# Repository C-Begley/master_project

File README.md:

# MEng Individual Project ENG5041PA Hardware and Software Emulation Testbed for CubeSat Design

## Abstract
CubeSats are praised for reducing the cost of access to space and increasing opportunities for universities and small organisations to carry out space related research. In principal, a small team with an innovative solution could rapidly develop and fly hardware in space using already existing building 'block' components. However, they still require technical electronic knowledge for the construction and testing of designs. While technical knowledge will always be required, especially on custom built CubeSats, this project aimed to reduce this barrier of entry, by providing a test bed framework to program and experiment with potential CubeSat designs.

The project has two main aims: the construction of physical devices for use in testing and developing accompanying software to help use these devices. The main physical device is a FlatSat, which aims to be generic and suitable for a range of projects. It uses PC/104 Plus connectors and has access to power and diagnostic connections. Alongside the FlatSat, there is a mainboard and battery board from an open source CubeSat design, which can be used to test other CubeSat subsystems. 

The project software helps schedule tasks to be run using the mainboard and FlatSat system. These tasks then act as emulations of an entire CubeSat subsystem. This allows for a subsystem to be tested, as if an entire CubeSat had already been constructed. The framework for programming and using this software, strives to be simple enough for those inexperienced with programming to be able to be use, while still giving enough complexity that most aspects of a CubeSat can be emulated.

To demonstrate the usability of the system, two demonstration boards have been constructed. These boards provide example emulations of payload and communication boards. They also provide a template that can be modified to construct and emulate other subsystems.  A demonstration task schedule has also been created to show how devices can interact with the software and mainboard from this project.

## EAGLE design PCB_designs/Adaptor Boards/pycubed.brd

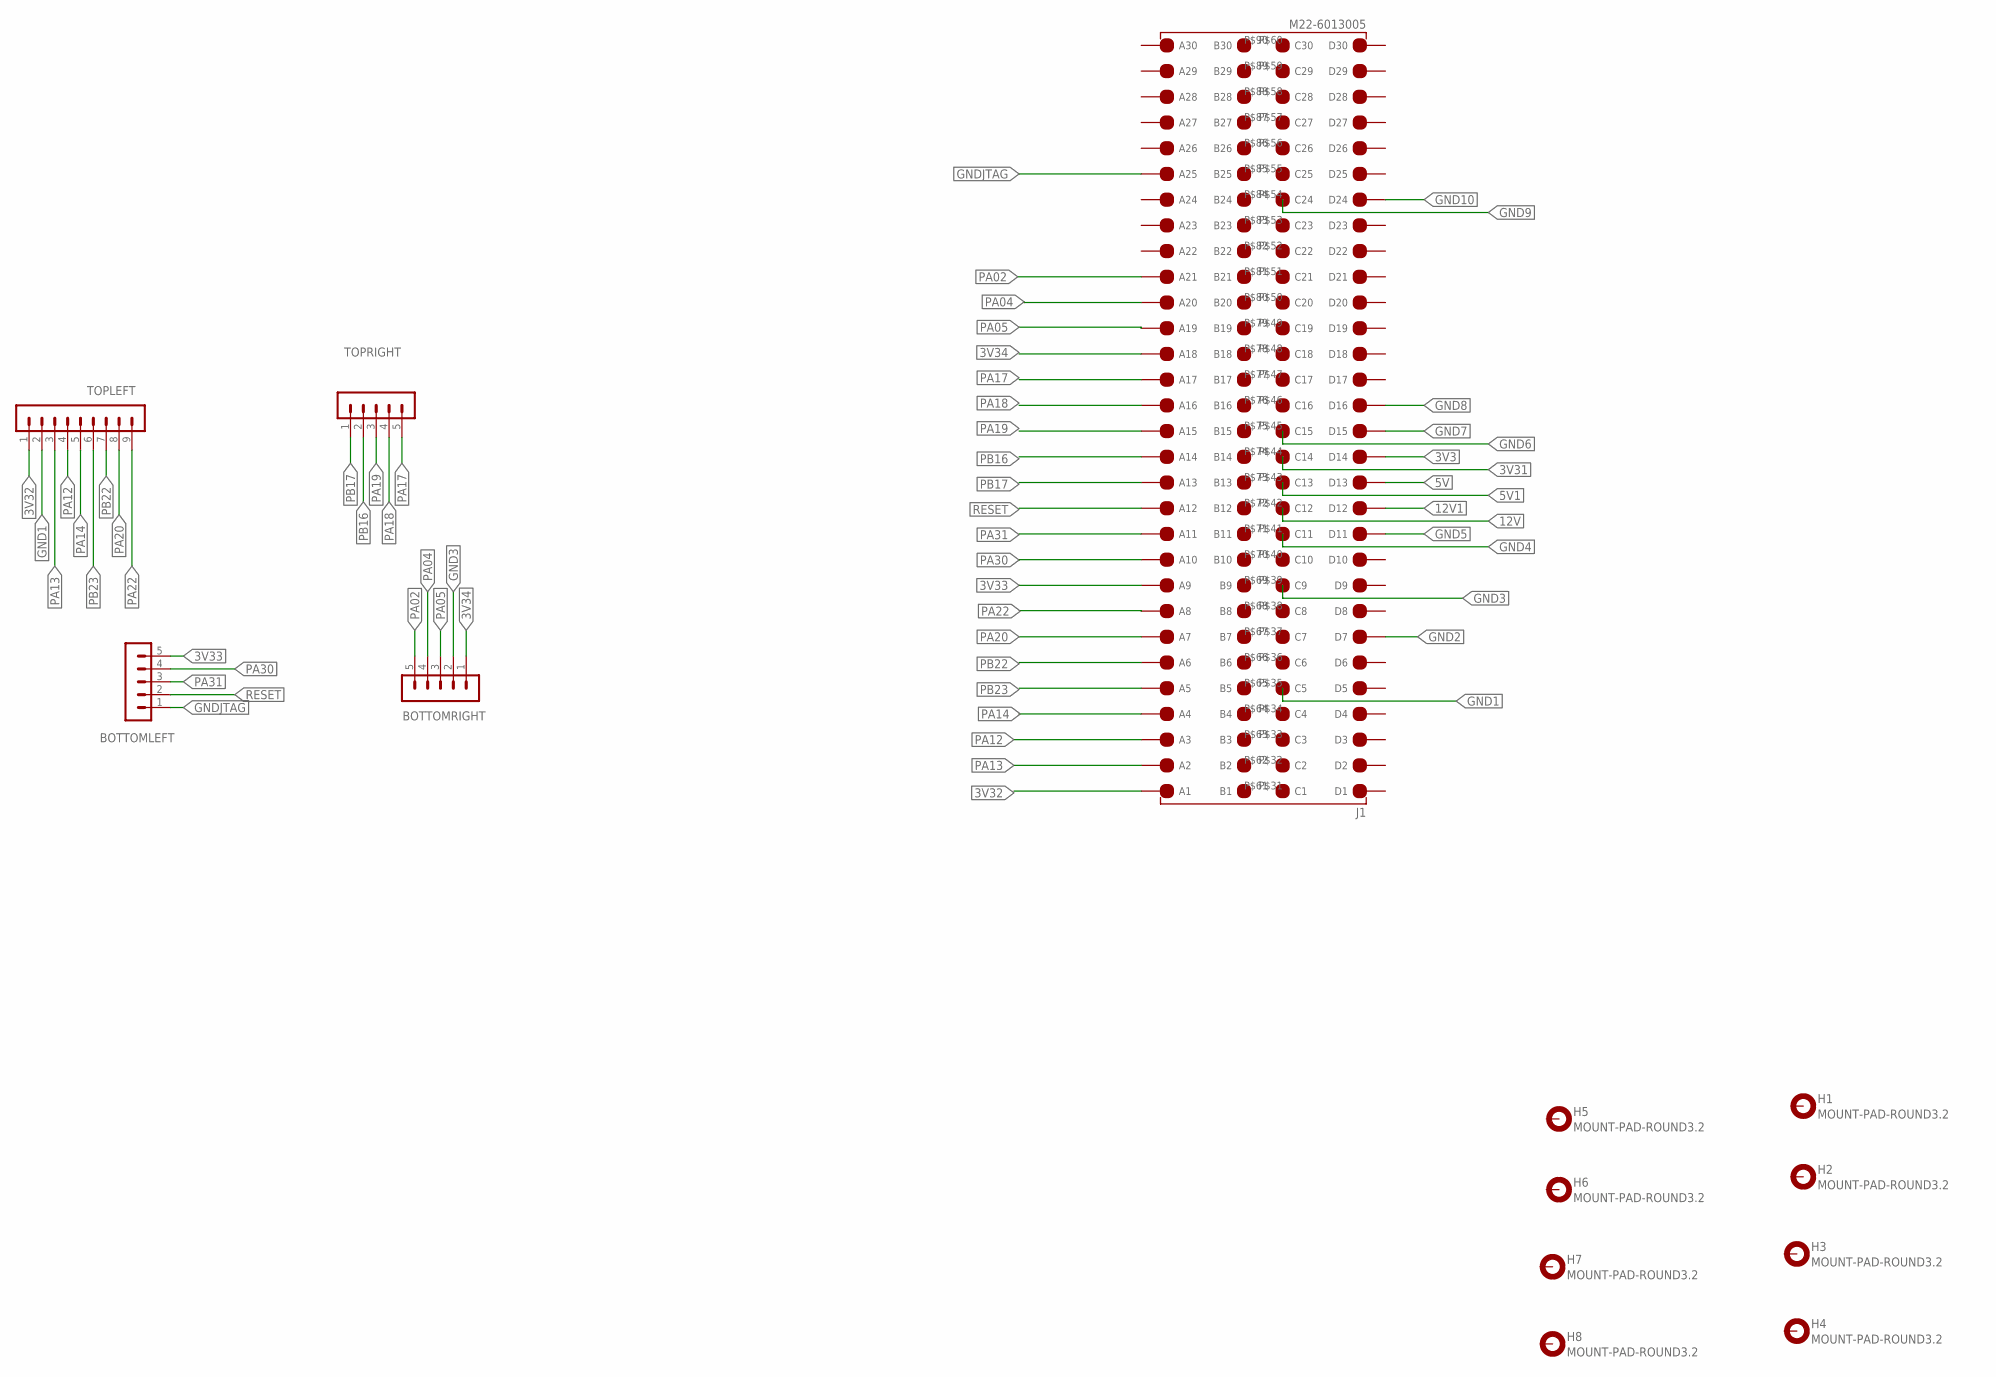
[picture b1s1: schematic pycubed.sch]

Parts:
BOTTOMLEFT: MA05-1
BOTTOMRIGHT: MA05-1
H1, H2, H3, H4, H5, H6, H7, H8: MOUNT-PAD-ROUND3.2; 3,2-PAD
J1: M22-6013005; RHDR120W55P200_4X30_6020X820X9
TOPLEFT: MA09-1
TOPRIGHT: MA05-1

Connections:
3V3: J1.P$14 (D14)
3V31: J1.P$44 (C14)
3V32: J1.P$91 (A1), TOPLEFT.1
3V33: BOTTOMLEFT.5, J1.P$99 (A9)
3V34: BOTTOMRIGHT.1, J1.P$108 (A18)
5V: J1.P$13 (D13)
5V1: J1.P$43 (C13)
12V: J1.P$42 (C12)
12V1: J1.P$12 (D12)
GND1: J1.P$35 (C5), TOPLEFT.2
GND2: J1.P$7 (D7)
GND3: BOTTOMRIGHT.2, J1.P$39 (C9)
GND4: J1.P$41 (C11)
GND5: J1.P$11 (D11)
GND6: J1.P$45 (C15)
GND7: J1.P$15 (D15)
GND8: J1.P$16 (D16)
GND9: J1.P$54 (C24)
GND10: J1.P$24 (D24)
GNDJTAG: BOTTOMLEFT.1, J1.P$115 (A25)
PA02: BOTTOMRIGHT.5, J1.P$111 (A21)
PA04: BOTTOMRIGHT.4, J1.P$110 (A20)
PA05: BOTTOMRIGHT.3, J1.P$109 (A19)
PA12: J1.P$93 (A3), TOPLEFT.4
PA13: J1.P$92 (A2), TOPLEFT.3
PA14: J1.P$94 (A4), TOPLEFT.5
PA17: J1.P$107 (A17), TOPRIGHT.5
PA18: J1.P$106 (A16), TOPRIGHT.4
PA19: J1.P$105 (A15), TOPRIGHT.3
PA20: J1.P$97 (A7), TOPLEFT.8
PA22: J1.P$98 (A8), TOPLEFT.9
PA30: BOTTOMLEFT.4, J1.P$100 (A10)
PA31: BOTTOMLEFT.3, J1.P$101 (A11)
PB16: J1.P$104 (A14), TOPRIGHT.2
PB17: J1.P$103 (A13), TOPRIGHT.1
PB22: J1.P$96 (A6), TOPLEFT.7
PB23: J1.P$95 (A5), TOPLEFT.6
RESET: BOTTOMLEFT.2, J1.P$102 (A12)

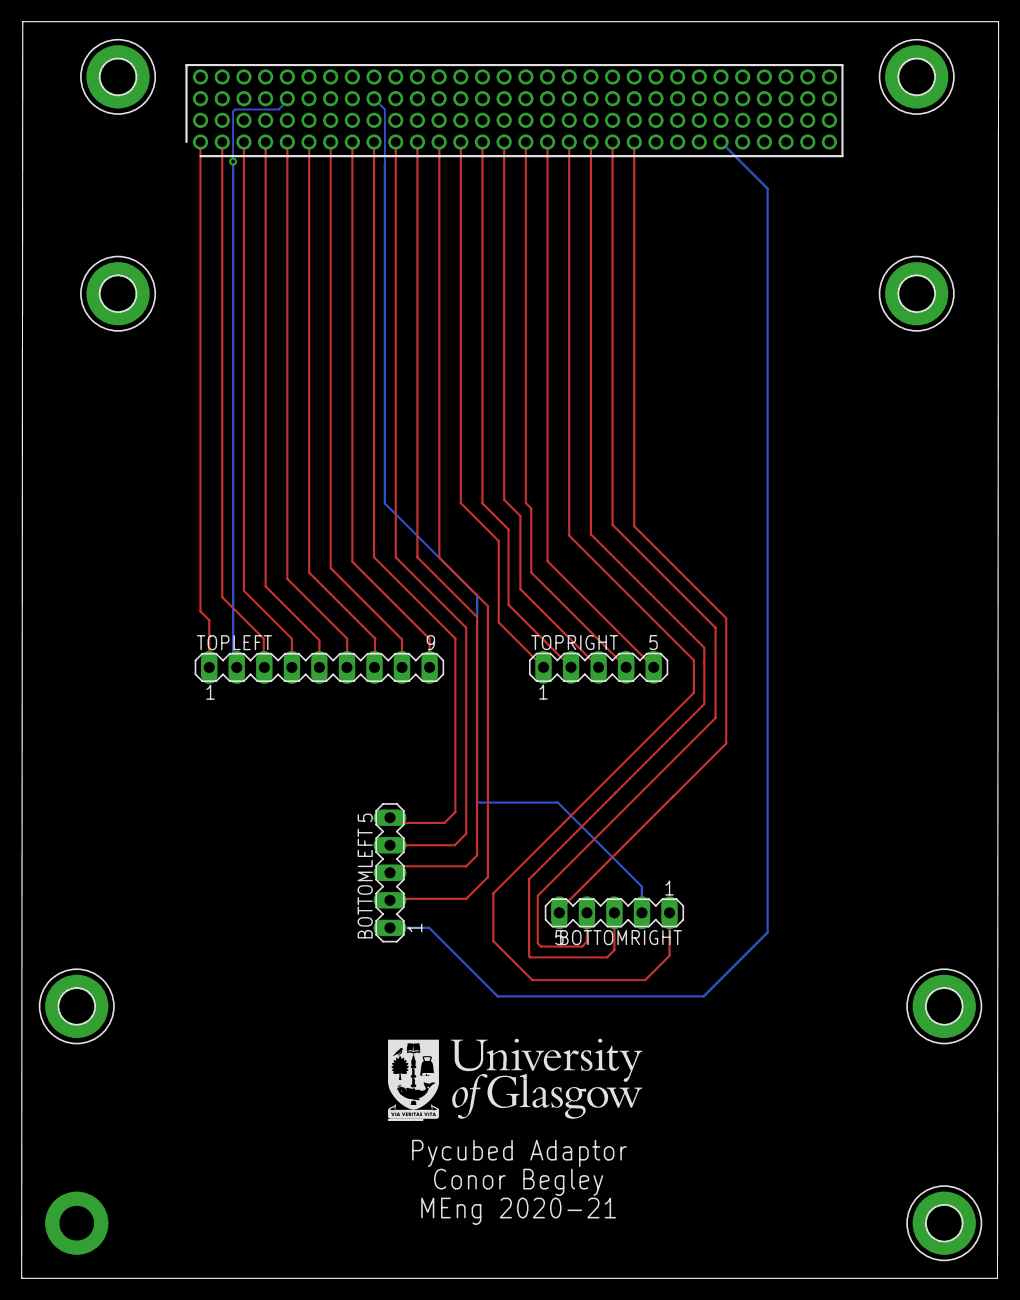
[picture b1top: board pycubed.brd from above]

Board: 2 copper layers, 90.1 x 115.9 mm, 13 parts (1 on the bottom side), 24 nets.

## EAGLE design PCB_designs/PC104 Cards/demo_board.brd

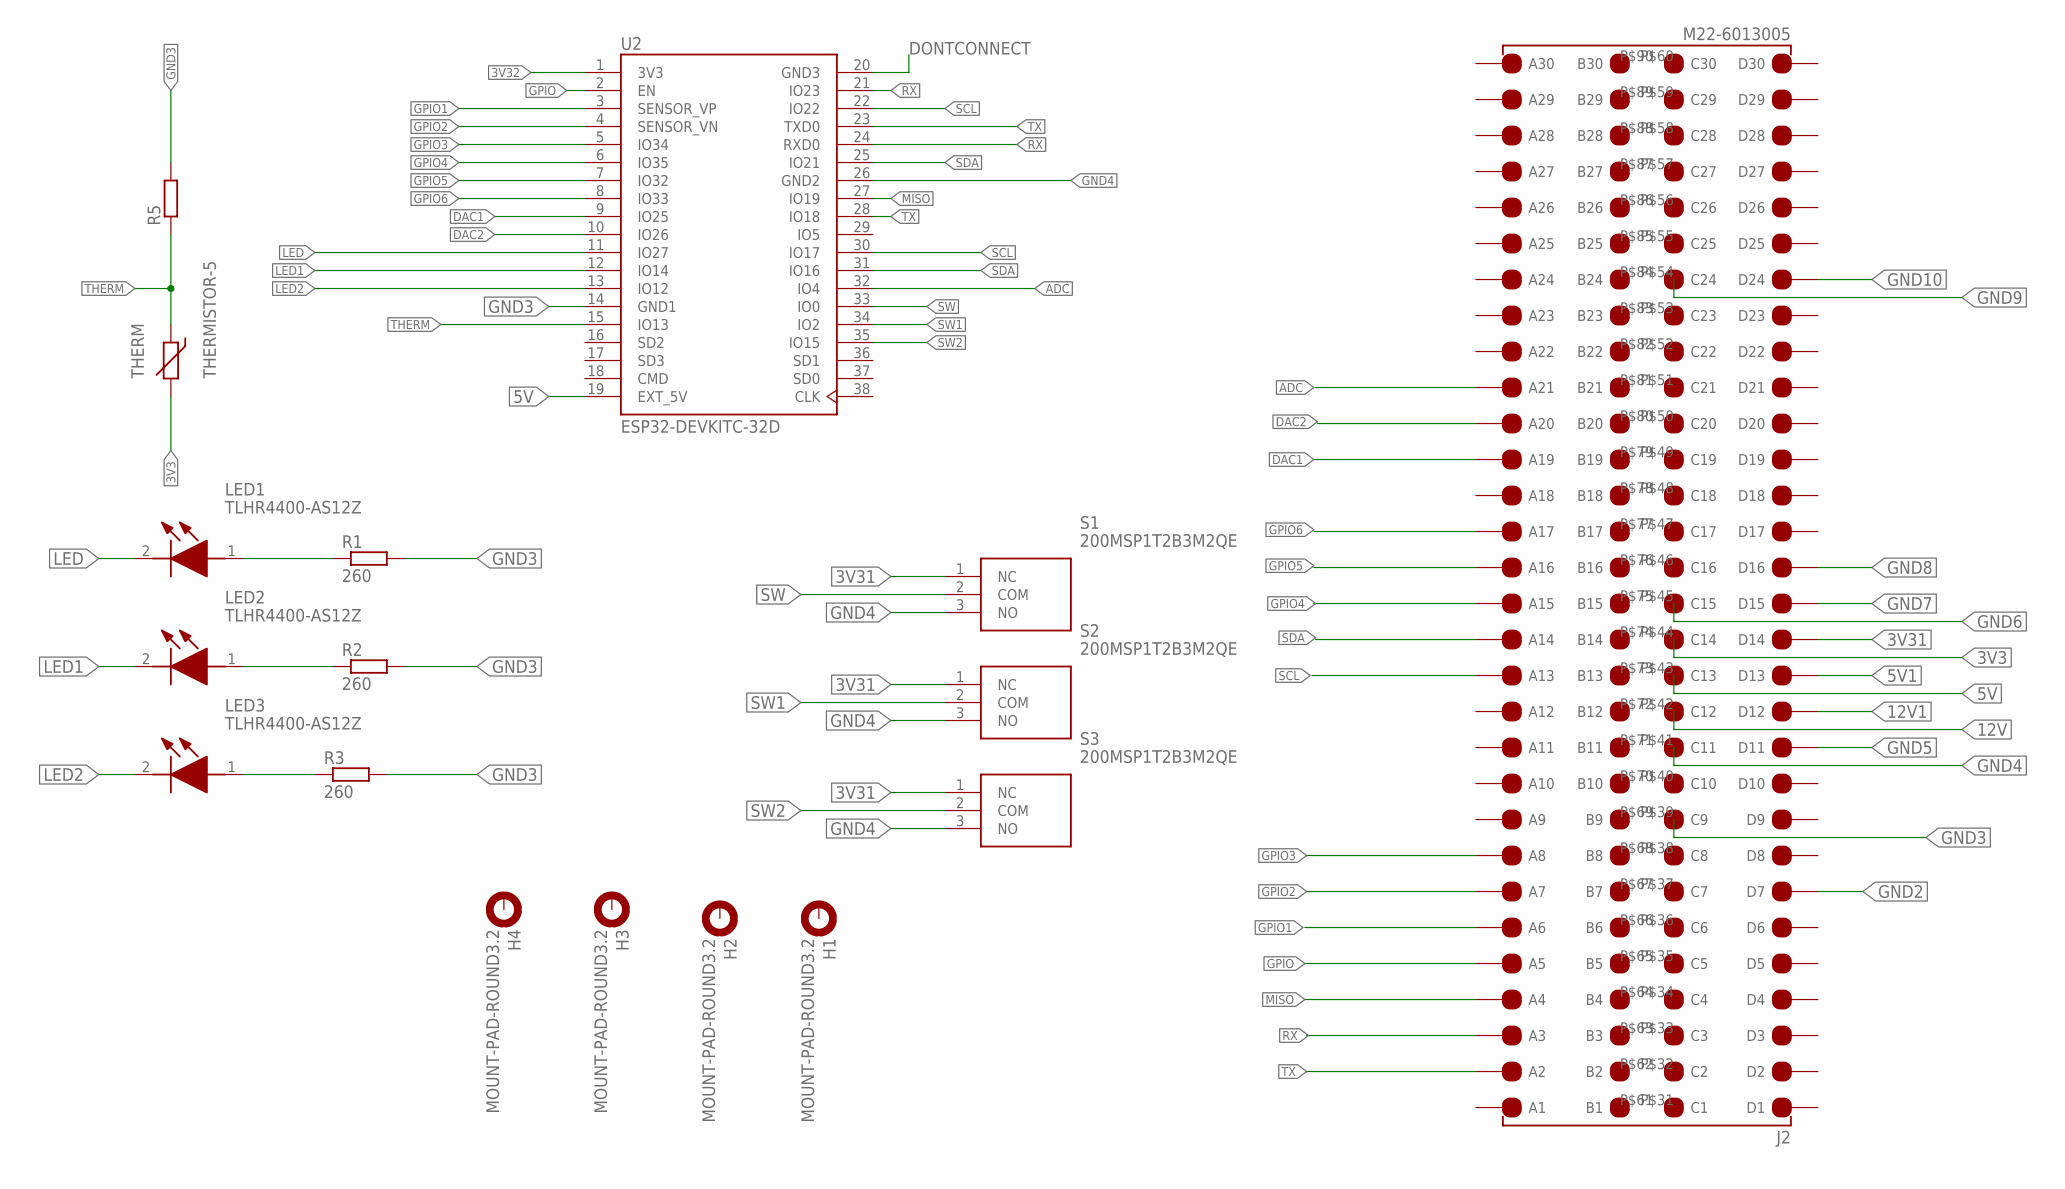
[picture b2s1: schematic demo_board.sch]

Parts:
H1, H2, H3, H4: MOUNT-PAD-ROUND3.2; 3,2-PAD
J2: M22-6013005; RHDR120W55P200_4X30_6020X820X9
LED1, LED2, LED3: TLHR4400-AS12Z; TLHR4400AS12Z
R1, R2, R3: 260; 0204/7
R5: 130; 0204/7
S1, S2, S3: 200MSP1T2B3M2QE
THERM: THERMISTOR-5; R-5
U2: ESP32-DEVKITC-32D; MODULE_ESP32-DEVKITC-32D

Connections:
3V3: J2.P$44 (C14), THERM.2
3V31: J2.P$14 (D14), S1.1 (NC), S2.1 (NC), S3.1 (NC)
3V32: U2.1 (3V3)
5V: J2.P$43 (C13), U2.19 (EXT_5V)
5V1: J2.P$13 (D13)
12V: J2.P$42 (C12)
12V1: J2.P$12 (D12)
ADC: J2.P$111 (A21), U2.32 (IO4)
DAC1: J2.P$109 (A19), U2.9 (IO25)
DAC2: J2.P$110 (A20), U2.10 (IO26)
DONTCONNECT: U2.20 (GND3)
GND2: J2.P$7 (D7)
GND3: J2.P$39 (C9), R1.2, R2.2, R3.2, R5.2, U2.14 (GND1)
GND4: J2.P$41 (C11), S1.3 (NO), S2.3 (NO), S3.3 (NO), U2.26 (GND2)
GND5: J2.P$11 (D11)
GND6: J2.P$45 (C15)
GND7: J2.P$15 (D15)
GND8: J2.P$16 (D16)
GND9: J2.P$54 (C24)
GND10: J2.P$24 (D24)
GPIO: J2.P$95 (A5), U2.2 (EN)
GPIO1: J2.P$96 (A6), U2.3 (SENSOR_VP)
GPIO2: J2.P$97 (A7), U2.4 (SENSOR_VN)
GPIO3: J2.P$98 (A8), U2.5 (IO34)
GPIO4: J2.P$105 (A15), U2.6 (IO35)
GPIO5: J2.P$106 (A16), U2.7 (IO32)
GPIO6: J2.P$107 (A17), U2.8 (IO33)
LED: LED1.2 (K), U2.11 (IO27)
LED1: LED2.2 (K), U2.12 (IO14)
LED2: LED3.2 (K), U2.13 (IO12)
MISO: J2.P$94 (A4), U2.27 (IO19)
unnamed: LED1.1 (A), R1.1
unnamed: LED2.1 (A), R2.1
unnamed: LED3.1 (A), R3.1
RX: J2.P$93 (A3), U2.21 (IO23), U2.24 (RXD0)
SCL: J2.P$103 (A13), U2.22 (IO22), U2.30 (IO17)
SDA: J2.P$104 (A14), U2.25 (IO21), U2.31 (IO16)
SW: S1.2 (COM), U2.33 (IO0)
SW1: S2.2 (COM), U2.34 (IO2)
SW2: S3.2 (COM), U2.35 (IO15)
THERM: R5.1, THERM.1, U2.15 (IO13)
TX: J2.P$92 (A2), U2.23 (TXD0), U2.28 (IO18)

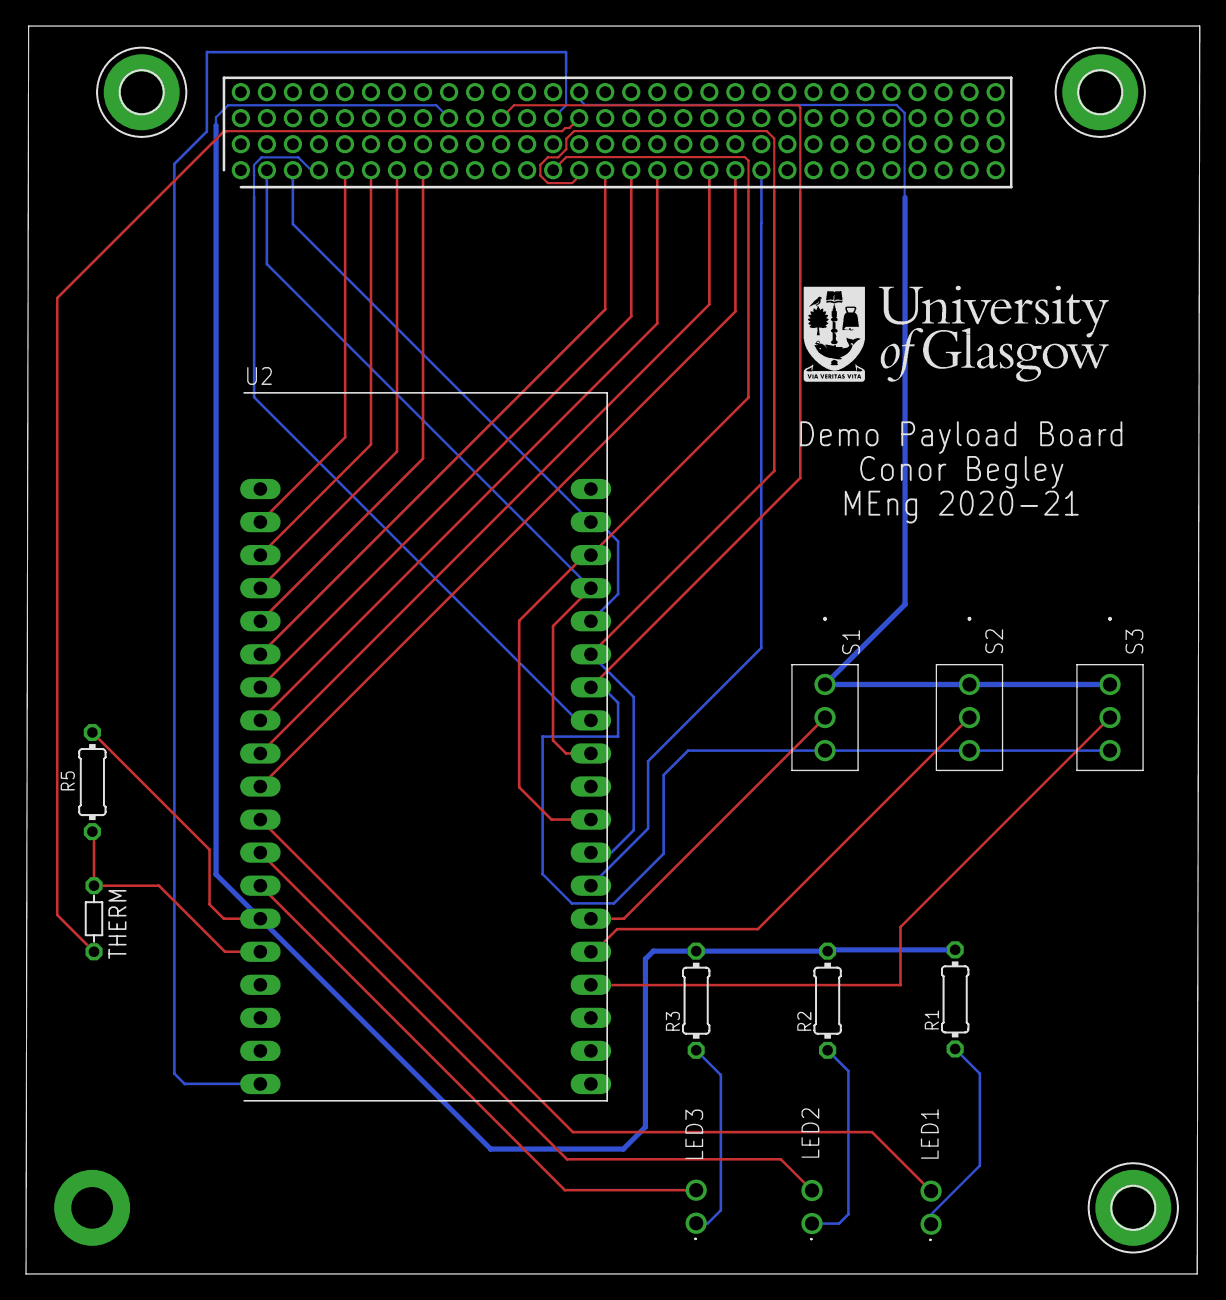
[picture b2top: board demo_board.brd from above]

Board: 2 copper layers, 90.2 x 95.9 mm, 17 parts (1 on the bottom side), 30 nets.

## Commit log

2020-11-09 Initial Board Designs
2020-11-09 Setup Software Directory
2020-11-09 Initial Code
    Currently working on implementing figuring out monotonic timeline
2020-11-10 First iteration of tasks scheduled
2020-11-10 Added initial fully scheduling with BUG
    Currently not scheduling up to full period, in part due to interval being added to the clock each turn
2020-11-11 Complete monotonic scheduling
2020-11-11 Inital runing of scheduled tasks
    Currently just printing the name of task at task interval
2020-11-15 Updated PCB Designs
2020-11-18 Updated PCB desgins to fix wiring mismatches
2020-11-18 Initial Screen Program ready for adding I2C
2020-11-24 First working scheduling using config file
2020-11-24 Config works with directory as well as file
2020-11-24 Updated to work with seperate files for each task
2020-11-24 Added default settings
2020-11-25 demo programs for ESP32
2020-11-25 Updated to load from file
2020-11-25 Updated to use scheduling steps to speed up scheduling time
2020-11-27 UART demo
2020-11-27 Updated to work with UART
2020-11-27 Fixed scheduling bug
2020-11-30 Added custom functions and tidier scheduler
2020-11-30 Added SPI
2020-12-01 Updated PyBoard and added demo files used previously
2020-12-01 Previously used files
2020-12-01 Updateed ploting demo
2020-12-03 First prototype payload
2020-12-03 Tidied to be I2C
2020-12-06 Demo programs I2C
2020-12-06 Working interupts
2021-01-08 Tidy_for_masters_thesis
2021-01-08 Updated to final Mainboard code
2021-01-13 Added missing timing files
2021-01-13 Refactored demo boards code
2021-01-13 Fixed errors in footprints
2021-01-13 Updated Title in ReadMe
2021-02-22 Final Handover
2021-02-27 Added License
